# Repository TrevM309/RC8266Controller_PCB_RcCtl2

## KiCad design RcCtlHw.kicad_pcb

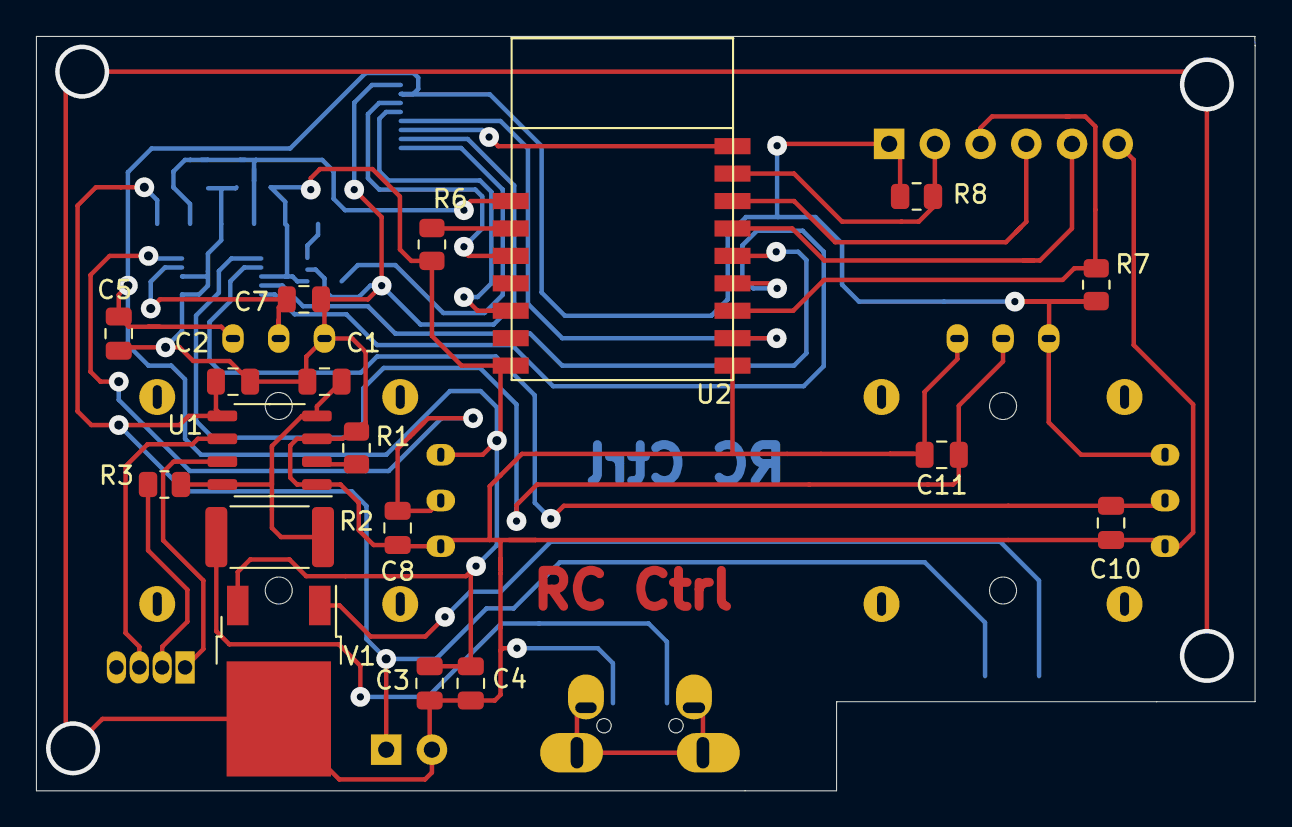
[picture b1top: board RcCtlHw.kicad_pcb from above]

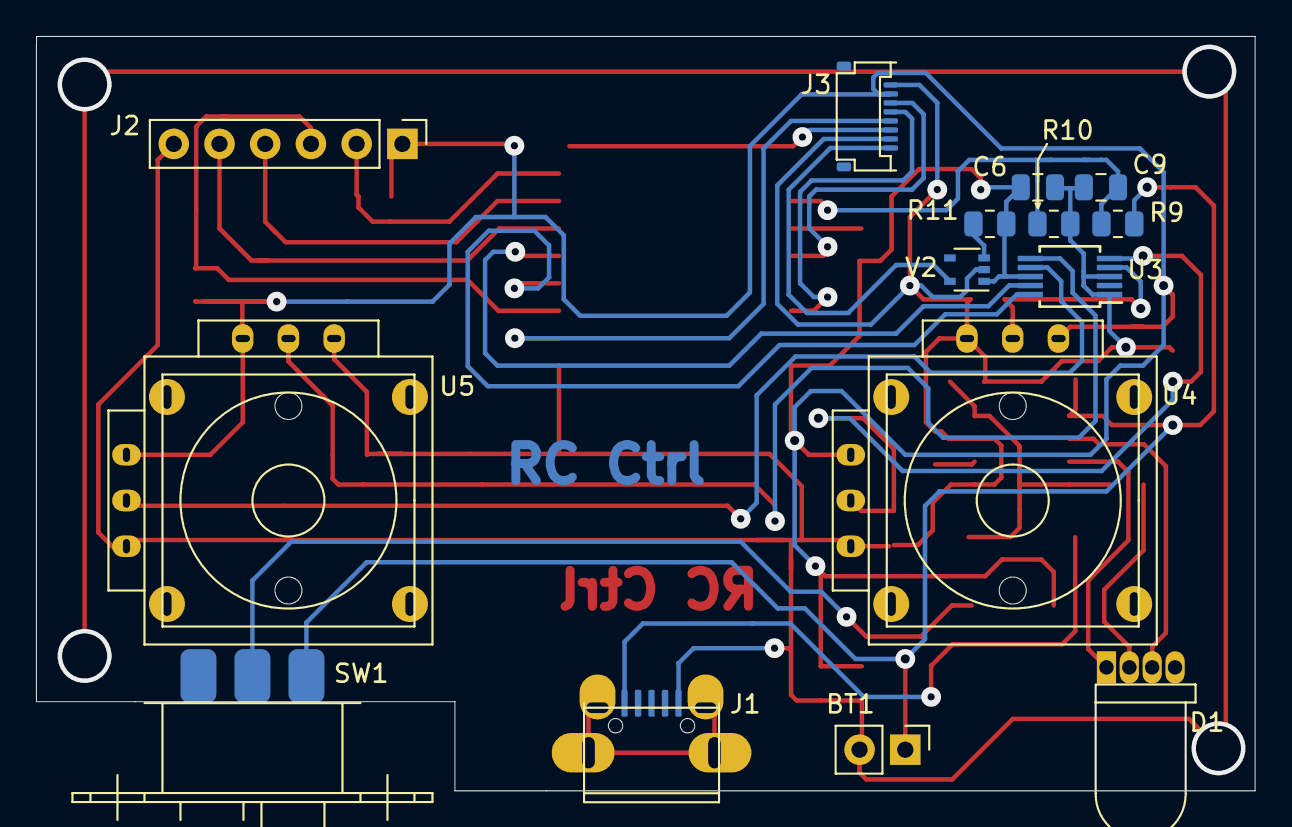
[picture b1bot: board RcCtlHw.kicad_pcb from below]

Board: 2 copper layers, 67.7 x 41.9 mm, 33 parts (15 on the bottom side), 28 nets.

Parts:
BT1: LiPo 3v7; PinHeader_1x02_P2.54mm_Vertical
C1, C2, C3, C4: 10u; C_0805_2012Metric
C5, C6, C7, C8, C9, C10, C11: 100n; C_0805_2012Metric
D1: Chg; LED_D5.0mm-4_RGB-RIGHT
J1: USB_B_Mini; USB_micro
J2: Program; PinHeader_1x06_P2.54mm_Vertical_bent
J3: TFT_LCD; 8w_FFC_conn
R1, R3: 1K2; R_0805_2012Metric
R2: 0.4; R_2512_6332Metric
R6, R7, R8, R9, R11: 10K; R_0805_2012Metric
R10: 1K; R_0805_2012Metric
SW1: On/Off; SlideSwitch
U1: TP4056; SOP-8_3.9x4.9mm_P1.27mm
U2: ESP-M2; ESP-M2_DOIT
U3: ADS1015; MSOP-10_3x3mm_P0.5mm
U4: Right Joystick; Joystick
U5: Left Joystick; Joystick
V1: 3V3; TO-252-2
V2: LDO_2V8; SOT-353_SC-70-5

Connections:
+3V3: C3.1, C4.1, C5.1, C6.1, J2.1, J3.7, R6.1, R7.1, R8.1, R11.1, U2.7, U3.8, U4.1, U4.4, U5.3, U5.4, V1.3, V2.1
+BATT: BT1.1, C2.1, R9.1, SW1.1, U1.5
/2V8_BackLight: J3.1, V2.5
/Flash: J2.3, R7.2, U2.10
/I2C_SCL: U2.11, U3.10
/I2C_SDA: U2.12, U3.9
/LH: C11.1, U3.6, U5.2
/LV: C10.1, U3.7, U5.5
/RH: C7.1, U3.4, U4.2
/RST: J2.2, R8.2, U2.15
/RV: C8.1, U3.5, U4.5
/RX: J2.5, U2.13
/TFT_RS: J3.4, U2.9
/TFT_RST: J3.3, U2.16
/TFT_SCL: J3.6, U2.3
/TFT_SDA: J3.5, U2.5
/TX: J2.4, U2.14
GND: BT1.2, C1.2, C2.2, C3.2, C4.2, C5.2, C6.2, C7.2, C8.2, C9.2, C10.2, C11.2, J1.5, J2.6, J3.2, J3.8, R1.1, R10.2, U1.1, U1.3, U2.8, U3.1, U3.3, U4.3, U4.6, U5.1, U5.6, V1.2, V2.2
unnamed: C1.1, R2.1, R3.2, U1.4, U1.8
unnamed: C9.1, R9.2, R10.1, U2.1
unnamed: D1.1, U1.7
unnamed: D1.2, R3.1
unnamed: D1.3, U1.6
unnamed: J1.1, R2.2
unnamed: R1.2, U1.2
unnamed: R6.2, U2.2
unnamed: R11.2, V2.3
unnamed: SW1.2, V1.1

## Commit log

2021-07-23 Ready to etch
2021-09-18 Added fixing holes, ready for making
